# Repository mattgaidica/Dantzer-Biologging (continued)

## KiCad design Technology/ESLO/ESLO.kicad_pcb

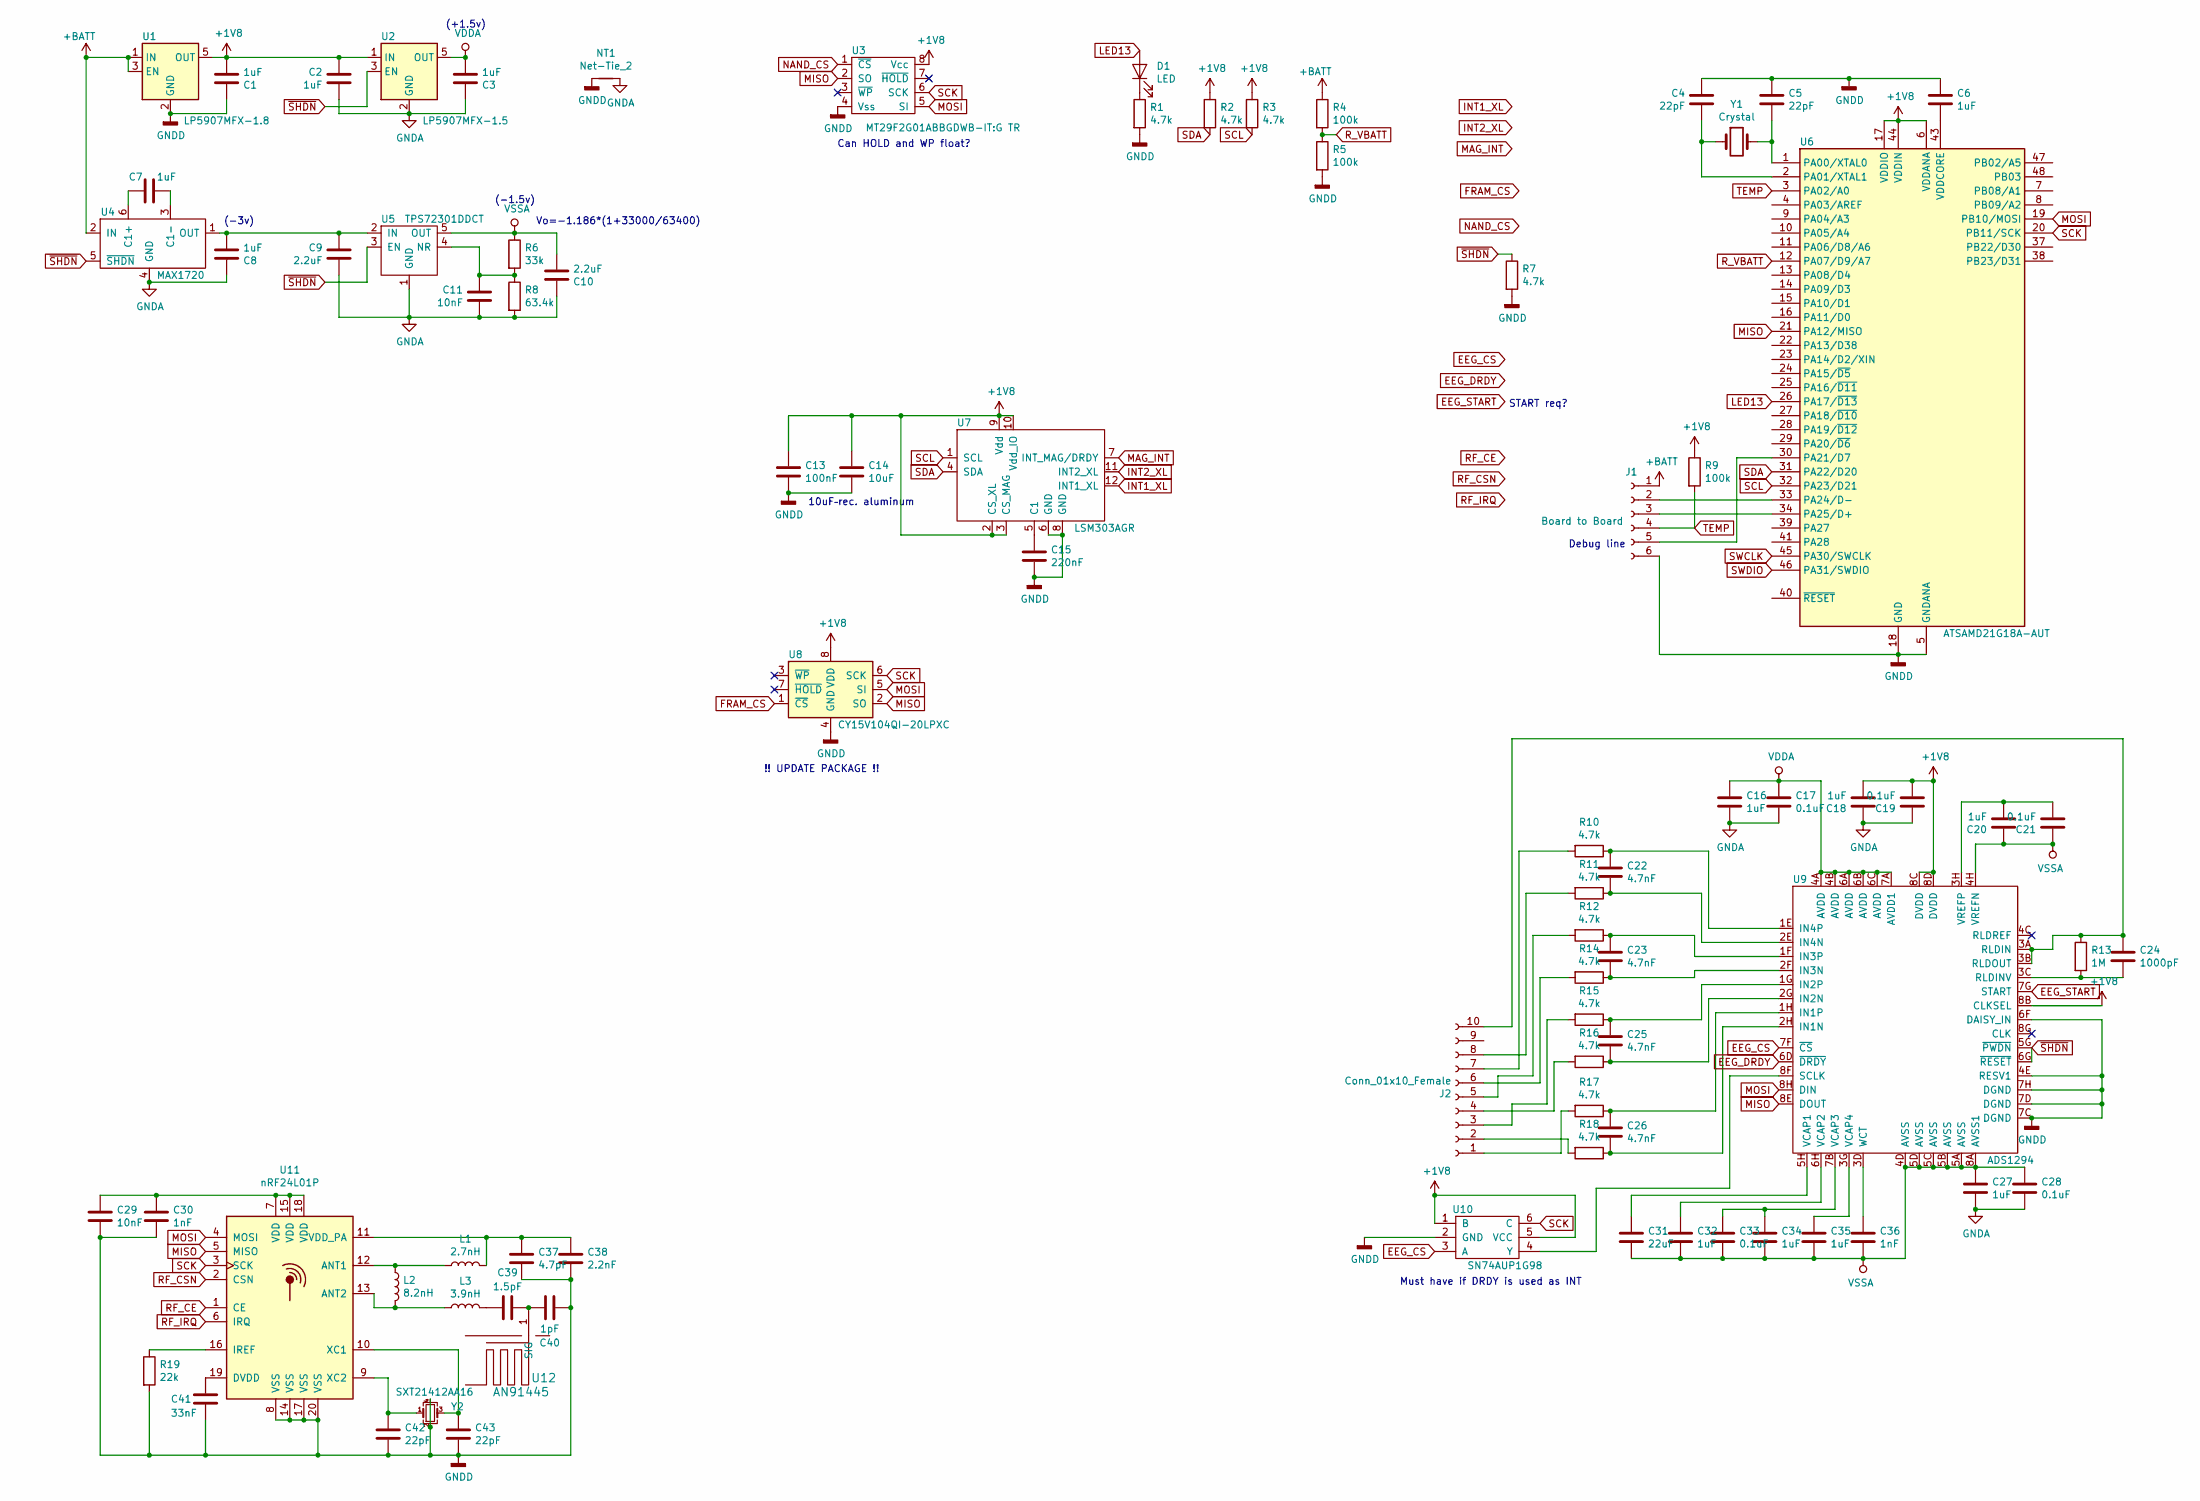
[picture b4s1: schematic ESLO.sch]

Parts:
C1, C2, C3, C6, C7, C8, C16, C18, C20, C27, C32, C34, C35: 1uF; C_0402_1005Metric
C4, C5, C42, C43: 22pF; C_0402_1005Metric
C9, C10: 2.2uF; C_0402_1005Metric
C11, C29: 10nF; C_0402_1005Metric
C13: 100nF; C_0402_1005Metric
C14: 10uF; C_0603_1608Metric; Digikey 490-14372-1-ND
C15: 220nF; C_0402_1005Metric
C17, C19, C21, C28, C33: 0.1uF; C_0402_1005Metric
C22, C23, C25, C26: 4.7nF; C_0402_1005Metric
C24: 1000pF; C_0402_1005Metric
C30, C36: 1nF; C_0402_1005Metric
C31: 22uF; C_0603_1608Metric; Digikey 1276-2867-1-ND
C37: 4.7pF; C_0402_1005Metric
C38: 2.2nF; C_0402_1005Metric
C39: 1.5pF; C_0402_1005Metric
C40: 1pF; C_0402_1005Metric
C41: 33nF; C_0402_1005Metric
D1: LED; LED_0603_1608Metric
J1: Board to Board; Hirose_DF52-6S-0.8H_1x06-1MP_P0.80mm_Horizontal
J2: Conn_01x10_Female; Hirose_DF52-10S-0.8H_1x10-1MP_P0.80mm_Horizontal
L1: 2.7nH; L_0402_1005Metric
L2: 8.2nH; L_0402_1005Metric
L3: 3.9nH; L_0402_1005Metric
NT1: Net-Tie_2; NetTie-2_SMD_Pad0.5mm
R1, R2, R3, R7, R16, R17, R18: 4.7k; R_0402_1005Metric
R4, R5, R9: 100k; LED_0402_1005Metric
R6: 33k; R_0402_1005Metric; Digikey A129645CT-ND
R8: 63.4k; R_0402_1005Metric; Digikey RHM63.4KBHCT-ND
R10, R11, R12, R14, R15: 4.7k; LED_0402_1005Metric
R13: 1M; LED_0402_1005Metric
R19: 22k; LED_0402_1005Metric
U1: LP5907MFX-1.8; SOT-23-5
U2: LP5907MFX-1.5; SOT-23-5; Digikey 296-40355-1-ND
U3: MT29F2G01ABBGDWB-IT:G TR; 8x6mm_WSON_UTSO; Digikey 557-1665-1-ND
U4: MAX1720; SOT-23-6
U5: TPS72301DDCT; SOT-23-5; Digikey 296-38438-1-ND
U6: ATSAMD21G18A-AUT; QFN-48-1EP_7x7mm_P0.5mm_EP5.15x5.15mm; Digikey ATSAMD21G18A-MFTCT-ND
U7: LSM303AGR; LGA-12_2x2mm_P0.5mm; Digikey 497-16527-1-ND
U8: CY15V104QI-20LPXC; DFN-8-1EP_3x3mm_P0.65mm_EP1.7x2.05mm
U9: ADS1294; BGA-64_8x8_8.0x8.0mm_ADS129x; Digikey 296-28024-1-ND
U10: SN74AUP1G98; SOT-563; Digikey 296-19087-1-ND
U11: nRF24L01P; QFN-20-1EP_4x4mm_P0.5mm_EP2.5x2.5mm
U12: AN91445; AN91445_MG
Y1: Crystal; Crystal_SMD_3215-2Pin_3.2x1.5mm; Digikey SER4103CT-ND
Y2: SXT21412AA16; SXT214

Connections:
+1V8: C1.1, C2.2, C13.1, C14.1, C18.2, C19.2, R2.1, R3.1, R9.1, U1.5 (OUT), U2.1 (IN), U3.8 (Vcc), U6.6 (VDDANA), U6.17 (VDDIO), U6.36 (VDDIO), U6.44 (VDDIN), U7.2 (CS_XL), U7.3 (CS_MAG), U7.9 (Vdd), U7.10 (Vdd_IO), U8.8 (VDD), U9.8B (CLKSEL), U9.8C (DVDD), U9.8D (DVDD), U10.1 (B), U10.5 (VCC)
D+: J1.3, U6.34 (PA25/D+)
D-: J1.2, U6.33 (PA24/D-)
EEG_CS: U6.15 (PA10/D1), U9.7F (~CS), U10.3 (A)
EEG_DRDY: U6.16 (PA11/D0), U9.6D (~DRDY)
EEG_START: U6.22 (PA13/D38), U9.7G (START)
FRAM_CS: U6.13 (PA08/D4), U8.1 (~CS)
GNDA: C2.1, C3.2, C8.2, C9.1, C10.2, C11.1, C16.2, C17.2, C18.1, C19.1, C27.2, C28.2, NT1.2, R8.2, U2.2 (GND), U4.4 (GND), U5.1 (GND)
GNDD: C1.2, C4.2, C5.1, C6.1, C13.2, C14.2, C15.1, C29.2, C30.2, C37.2, C38.2, C40.1, C41.1, C42.2, C43.2, J1.6, NT1.1, R1.2, R5.2, R7.2, R19.2, U1.2 (GND), U3.4 (Vss), U6.5 (GNDANA), U6.18 (GND), U6.35 (GND), U6.42 (GND), U7.6 (GND), U7.8 (GND), U8.4 (GND), U9.4E (RESV1), U9.6F (DAISY_IN), U9.7C (DGND), U9.7D (DGND), U9.7H (DGND), U10.2 (GND), U11.8 (VSS), U11.14 (VSS), U11.17 (VSS), U11.20 (VSS), U12.2, Y2.2, Y2.4
INT2_XL: U6.29 (PA20/~D6), U7.11 (INT2_XL)
LED13: D1.2 (A), U6.26 (PA17/~D13)
MAG_INT: U6.28 (PA19/~D12), U7.7 (INT_MAG/DRDY)
MISO: U3.2 (SO), U6.21 (PA12/MISO), U8.2 (SO), U9.8E (DOUT), U11.5 (MISO)
MOSI: U3.5 (SI), U6.19 (PB10/MOSI), U8.5 (SI), U9.8H (DIN), U11.4 (MOSI)
NAND_CS: U3.1 (~CS), U6.14 (PA09/D3)
unnamed: C4.1, U6.2 (PA01/XTAL1), Y1.1
unnamed: C5.2, U6.1 (PA00/XTAL0), Y1.2
unnamed: C6.2, U6.43 (VDDCORE)
unnamed: C7.1, U4.6 (C1+)
unnamed: C7.2, U4.3 (C1-)
unnamed: C8.1, C9.2, U4.1 (OUT), U5.2 (IN)
unnamed: C11.2, R6.2, R8.1, U5.4 (NR)
unnamed: C15.2, U7.5 (C1)
unnamed: C20.2, C21.2, U9.3H (VREFP)
unnamed: C22.1, R10.1, U9.1E (IN4P)
unnamed: C22.2, R11.1, U9.2E (IN4N)
unnamed: C23.1, R12.1, U9.1F (IN3P)
unnamed: C23.2, R14.1, U9.2F (IN3N)
unnamed: C24.1, J2.10, R13.1, U9.3A (RLDIN), U9.3B (RLDOUT)
unnamed: C24.2, R13.2, U9.3C (RLDINV)
unnamed: C25.1, R15.1, U9.1G (IN2P)
unnamed: C25.2, R16.1, U9.2G (IN2N)
unnamed: C26.1, R17.1, U9.1H (IN1P)
unnamed: C26.2, R18.1, U9.2H (IN1N)
unnamed: C31.1, U9.5H (VCAP1)
unnamed: C32.1, U9.6H (VCAP2)
unnamed: C33.1, C34.1, U9.7B (VCAP3)
unnamed: C35.1, U9.3G (VCAP4)
unnamed: C36.1, U9.3D (WCT)
unnamed: C37.1, C38.1, L1.2, U11.11 (VDD_PA)
unnamed: C39.1, L3.2
unnamed: C39.2, C40.2, U12.1
unnamed: C41.2, U11.19 (DVDD)
unnamed: C42.1, U11.9 (XC2), Y2.1
unnamed: C43.1, U11.10 (XC1), Y2.3
unnamed: D1.1 (K), R1.1
unnamed: J2.1, R17.2
unnamed: J2.2, R18.2
unnamed: J2.3, R15.2
unnamed: J2.4, R16.2
unnamed: J2.5, R12.2
unnamed: J2.6, R14.2
unnamed: J2.7, R10.2
unnamed: J2.8, R11.2
unnamed: L1.1, L2.1, U11.12 (ANT1)
unnamed: L2.2, L3.1, U11.13 (ANT2)
unnamed: R19.1, U11.16 (IREF)
unnamed: U9.8F (SCLK), U10.4 (Y)
RF_CE: U6.24 (PA15/~D5), U11.1 (CE)
RF_CSN: U6.23 (PA14/D2/XIN), U11.2 (CSN)
RF_IRQ: U6.25 (PA16/~D11), U11.6 (IRQ)
R_VBATT: R4.2, R5.1, U6.12 (PA07/D9/A7)
SCK: U3.6 (SCK), U6.20 (PB11/SCK), U8.6 (SCK), U10.6 (C), U11.3 (SCK)
SCL: R3.2, U6.32 (PA23/D21), U7.1 (SCL)
SDA: R2.2, U6.31 (PA22/D20), U7.4 (SDA)
SWCLK: U6.45 (PA30/SWCLK); also elsewhere on the board
SWDIO: U6.46 (PA31/SWDIO); also elsewhere on the board
TEMP: J1.4, R9.2, U6.3 (PA02/A0), U6.10 (PA05/A4)
VDDA: C3.1, C16.1, C17.1, U2.5 (OUT), U9.4A (AVDD), U9.4B (AVDD), U9.6A (AVDD), U9.6B (AVDD), U9.6C (AVDD), U9.7A (AVDD1)
VSSA: C10.1, C20.1, C21.1, C27.1, C28.1, C31.2, C32.2, C33.2, C34.2, C35.2, C36.2, R6.1, U5.5 (OUT), U9.4D (AVSS), U9.4H (VREFN), U9.5A (AVSS), U9.5B (AVSS), U9.5C (AVSS), U9.5D (AVSS), U9.8A (AVSS1)
~SHDN: R7.1, U2.3 (EN), U4.5 (~SHDN), U5.3 (EN), U6.11 (PA06/D8/A6), U9.5G (~PWDN), U9.6G (~RESET)

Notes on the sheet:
Vo=-1.186*(1+33000/63400)
Can HOLD and WP float?
(-1.5v)
(+1.5v)
10uF–rec. aluminum
Must have if DRDY is used as INT
!! UPDATE PACKAGE !!
(-3v)
Debug line
START req?

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
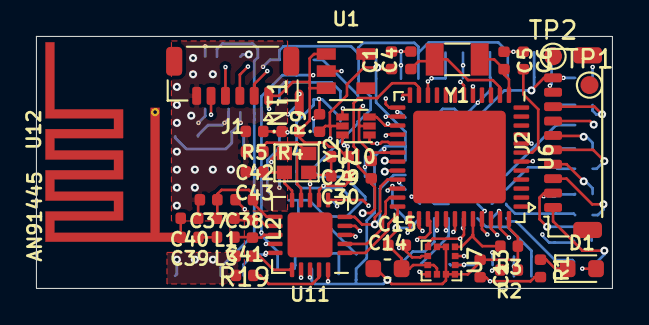
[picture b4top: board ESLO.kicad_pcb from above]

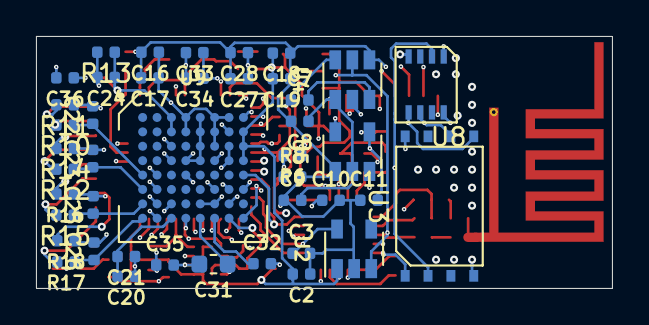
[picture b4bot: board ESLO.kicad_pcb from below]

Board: 4 copper layers, 32.0 x 14.0 mm, 84 parts (43 on the bottom side), 74 nets.

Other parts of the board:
TP1, TP2: TestPoint; TestPoint_Pad_D1.0mm

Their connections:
SWCLK: TP1.1; also elsewhere on the board
SWDIO: TP2.1; also elsewhere on the board

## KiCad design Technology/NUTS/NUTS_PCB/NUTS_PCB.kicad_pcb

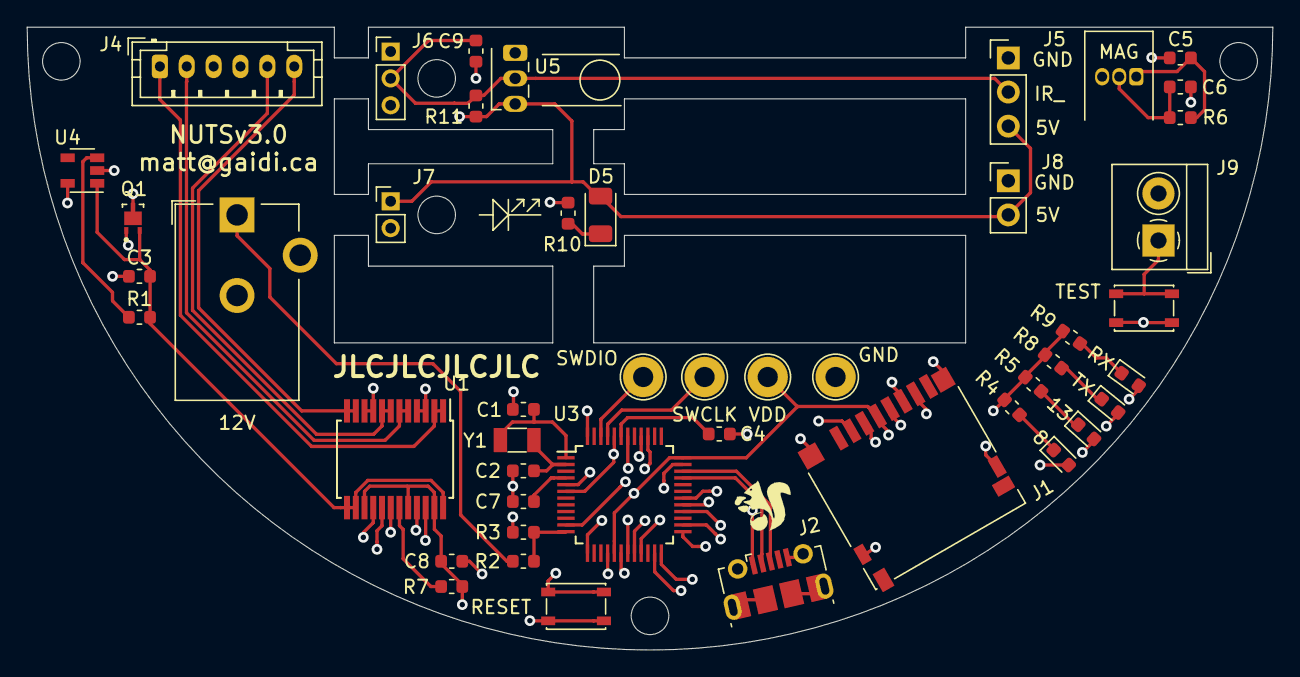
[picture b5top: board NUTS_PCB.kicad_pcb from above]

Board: 4 copper layers, 92.7 x 46.4 mm, 47 parts (1 on the bottom side), 41 nets.

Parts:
C1, C2: 22pF; C_0603_1608Metric
C3, C8: 10uF; C_0603_1608Metric
C4, C7: 1uF; C_0603_1608Metric
C5, C6: 100nF; C_0603_1608Metric
C9: .22uF; C_0603_1608Metric
D1, D2, D3, D4: LED; LED_0603_1608Metric
D5: IR_LED; LED_1206_3216Metric
J1: Micro_SD_Card_Det_Hirose_DM3AT; microSD_HC_Hirose_DM3D-SF
J2: USB_B_Micro; USB_Micro-B_Molex-105017-0001
J3: Jack-DC; BarrelJack_CUI_PJ-102AH_Horizontal
J4: Conn_01x06_Female; JST_PH_B6B-PH-K_1x06_P2.00mm_Vertical
J5: Conn_01x03_Male; PinHeader_1x03_P2.54mm_Vertical
J6: Conn_01x03_Female; PinHeader_1x03_P2.00mm_Vertical
J7: Conn_01x02_Female; PinHeader_1x02_P2.00mm_Vertical
J8: Conn_01x02_Male; PinHeader_1x02_P2.54mm_Vertical
J9: Screw_Terminal_01x02; TerminalBlock_4Ucon_1x02_P3.50mm_Horizontal
Q1: DMG3415UFY4Q; TRANS_DMG3415UFY4Q-7
R1, R2, R6, R7: 10K; R_0603_1608Metric
R3, R4, R5, R8, R9: 1K; R_0603_1608Metric
R10: 220; R_0603_1608Metric
R11: 390; R_0603_1608Metric
SW1, SW2: SW_SPST; SW_SPST_PTS810
TP1: SWDIO; TestPoint_Loop_D2.54mm_Drill1.5mm_Beaded
TP2: SWCLK; TestPoint_Loop_D2.54mm_Drill1.5mm_Beaded
TP3: VDD; TestPoint_Loop_D2.54mm_Drill1.5mm_Beaded
TP4: GND; TestPoint_Loop_D2.54mm_Drill1.5mm_Beaded
U1: TB6612FNG; SSOP-24_5.3x8.2mm_P0.65mm
U2: US5881; TO-92Flat
U3: ATSAMD21G18A-AUT; TQFP-48_7x7mm_P0.5mm
U4: SPX3819M5-L; SOT-23-5
U5: QSE159; ONSemi_QSE15x
Y1: Crystal; Crystal_SMD_3215-2Pin_3.2x1.5mm

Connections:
+5V: C8.1, D5.2, J2.1, J5.3, J6.1, J7.1, J8.2, R7.2, R11.1, U1.15, U1.20, U1.23, U5.3
+12V: C3.1, Q1.2, R1.1, U1.13, U1.14, U1.24, U4.1
+BATT: J3.1, Q1.3, R2.1
AIN1: U1.21, U3.29
AIN2: U1.22, U3.30
BIN1: U1.17, U3.25
BIN2: U1.16, U3.28
D0: J9.1, SW2.2, U3.16
D2: C6.1, R6.2, U2.2, U3.23
D8: D1.2, U3.11
D9: R2.2, R3.1, U3.12
D13: D2.2, U3.26
D+: J2.3, U3.34
D-: J2.2, U3.33
GND: C1.2, C2.2, C3.2, C4.2, C5.2, C6.2, C7.2, C8.2, C9.2, J1.6, J1.11, J2.5, J2.6, J3.2, J4.3, J4.4, J5.1, J6.3, J7.2, J8.1, J9.2, Q1.1, R3.2, R4.2, R5.2, R8.2, R9.2, R10.2, SW1.1, SW2.1, TP4.1, U1.3, U1.4, U1.9, U1.10, U1.18, U2.3, U3.5, U3.18, U3.35, U3.42, U4.2, U5.1
IR_DET: C9.1, J5.2, J6.2, R11.2, U3.24, U5.2
MISO: J1.7, U3.21
MOSI: J1.3, U3.19
unnamed: C1.1, U3.1, Y1.1
unnamed: C2.1, U3.2, Y1.2
unnamed: C4.1, U3.43
unnamed: C7.1, U3.4
unnamed: D1.1, R4.1
unnamed: D2.1, R5.1
unnamed: D3.1, R8.1
unnamed: D4.1, R9.1
unnamed: D5.1, R10.1
unnamed: J4.1, U1.1, U1.2
unnamed: J4.2, U1.5, U1.6
unnamed: J4.5, U1.7, U1.8
unnamed: J4.6, U1.11, U1.12
unnamed: R1.2, U4.3
unnamed: R7.1, U1.19
unnamed: SW1.2, U3.40
unnamed: TP1.1, U3.46
unnamed: TP2.1, U3.45
RXLED: D4.2, U3.48
SCK: J1.5, U3.20
SD_CS: J1.2, U3.13
TXLED: D3.2, U3.39
VDD: C5.1, J1.4, R6.1, TP3.1, U2.1, U3.6, U3.17, U3.36, U3.44, U4.5

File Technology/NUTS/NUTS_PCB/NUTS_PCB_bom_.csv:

Component,Description,Part,References,Value,Footprint,Quantity Per PCB,Datasheet,digikey
1,Unpolarized capacitor,C,C9,.22uF,C_0603_1608Metric,1,~,399-1102-1-ND
2,Unpolarized capacitor,C,C5 C6,100nF,C_0603_1608Metric,2,~,399-1100-1-ND
3,Unpolarized capacitor,C,C3 C8,10uF,C_0603_1608Metric,2,~,490-10474-1-ND
4,Unpolarized capacitor,C,C4 C7,1uF,C_0603_1608Metric,2,~,399-1100-1-ND
5,Unpolarized capacitor,C,C1 C2,22pF,C_0603_1608Metric,2,~,399-7874-1-ND
6,Light emitting diode,LED,D5,IR_LED,LED_1206_3216Metric,1,~,1497-1422-1-ND
7,Light emitting diode,LED,D1 D2 D3 D4,LED,LED_0603_1608Metric,4,~,
8,"Generic connector, single row, 01x02, script generated (kicad-library-utils/schlib/autogen/connector/)",Conn_01x02_Female,J7,Conn_01x02_Female,PinHeader_1x02_P2.00mm_Vertical,1,~,
9,"Generic connector, single row, 01x02, script generated (kicad-library-utils/schlib/autogen/connector/)",Conn_01x02_Male,J8,Conn_01x02_Male,PinHeader_1x02_P2.54mm_Vertical,1,~,A19430-ND
10,"Generic connector, single row, 01x03, script generated (kicad-library-utils/schlib/autogen/connector/)",Conn_01x03_Female,J6,Conn_01x03_Female,PinHeader_1x03_P2.00mm_Vertical,1,~,
11,"Generic connector, single row, 01x03, script generated (kicad-library-utils/schlib/autogen/connector/)",Conn_01x03_Male,J5,Conn_01x03_Male,PinHeader_1x03_P2.54mm_Vertical,1,~,A19423-ND
12,"Generic connector, single row, 01x06, script generated (kicad-library-utils/schlib/autogen/connector/)",Conn_01x06_Female,J4,Conn_01x06_Female,JST_PH_B6B-PH-K_1x06_P2.00mm_Vertical,1,~,455-2923-ND
13,DC Barrel Jack,Jack-DC,J3,Jack-DC,BarrelJack_CUI_PJ-102AH_Horizontal,1,~,CP-102A-ND
14,Micro SD Card Socket with card detection pins,Micro_SD_Card_Det_Hirose_DM3AT,J1,Micro_SD_Card_Det_Hirose_DM3AT,microSD_HC_Hirose_DM3D-SF,1,https://www.hirose.com/product/en/download_file/key_name/DM3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,HR1964CT-ND
15,"Generic screw terminal, single row, 01x02, script generated (kicad-library-utils/schlib/autogen/connector/)",Screw_Terminal_01x02,J9,Screw_Terminal_01x02,TerminalBlock_4Ucon_1x02_P3.50mm_Horizontal,1,~,277-1721-ND
16,USB Micro Type B connector,USB_B_Micro,J2,USB_B_Micro,USB_Micro-B_Molex-105017-0001,1,~,WM1399CT-ND
17,"P-JFET transistor, gate/source/drain",Q_PJFET_GSD,Q1,DMG3415UFY4Q,TRANS_DMG3415UFY4Q-7,1,~,DMG3415UFY4Q-7DICT-ND
18,Resistor,R,R1 R2 R6 R7,10K,R_0603_1608Metric,4,~,311-10KGRCT-ND
19,Resistor,R,R3 R4 R5 R8 R9,1K,R_0603_1608Metric,5,~,311-1.0KGRCT-ND
20,Resistor,R,R10,220,R_0603_1608Metric,1,~,311-220HRCT-ND
21,Resistor,R,R11,390,R_0603_1608Metric,1,~,A129683CT-ND
22,Single Pole Single Throw (SPST) switch,SW_SPST,SW1 SW2,SW_SPST,SW_SPST_PTS810,2,~,CKN10502CT-ND
23,"SAM D21 Microchip SMART ARM-based Flash MCU, 48Mhz, 256K Flash, 32K SRAM, TQFP-48",ATSAMD21G18A-AUT,U3,ATSAMD21G18A-AUT,TQFP-48_7x7mm_P0.5mm,1,http://ww1.microchip.com/downloads/en/DeviceDoc/SAMD21-Famil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,ATSAMD21G18A-AUTCT-ND
24,Plastic Silicon Photosensor,QSE159,U5,QSE159,ONSemi_QSE15x,1,http://www.onsemi.com/pub/Collateral/QSE159-D.pdf,QSE159-ND
25,"500mA Low drop-out regulator, Adjustable, SOT-23-5",SPX3819M5-L,U4,SPX3819M5-L,SOT-23-5,1,https://www.exar.com/content/document.ashx?id=22106&language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,1016-1873-1-ND
26,,TB6612FNG,U1,TB6612FNG,SSOP-24_5.3x8.2mm_P0.65mm,1,,TB6612FNGC8ELCT-ND
27,"Hall effect switch, unipolar, Bop=100G, Brp=45G, -40C to +85C",A1101ELHL,U2,US5881,TO-92Flat,1,http://www.allegromicro.com/en/Products/Part_Numbers/1101/1101.pdf,US5881LUA-AAA-000-BU-ND
28,Two pin crystal,Crystal,Y1,Crystal,Crystal_SMD_3215-2Pin_3.2x1.5mm,1,~,SER4103CT-ND





Component Groups:,28
Component Count:,43
Fitted Components:,43
Number of PCBs:,1
Total components:,43
Schematic Version:,
Schematic Date:,
BoM Date:,"Tuesday, March 24, 2020 at 10:09:05 PM"
Schematic Source:,/Users/matt/Box Sync/Biologging/Technology/NUTS/NUTS_PCB/NUTS_PCB.sch
KiCad Version:,Eeschema (5.1.5-0-10_14)

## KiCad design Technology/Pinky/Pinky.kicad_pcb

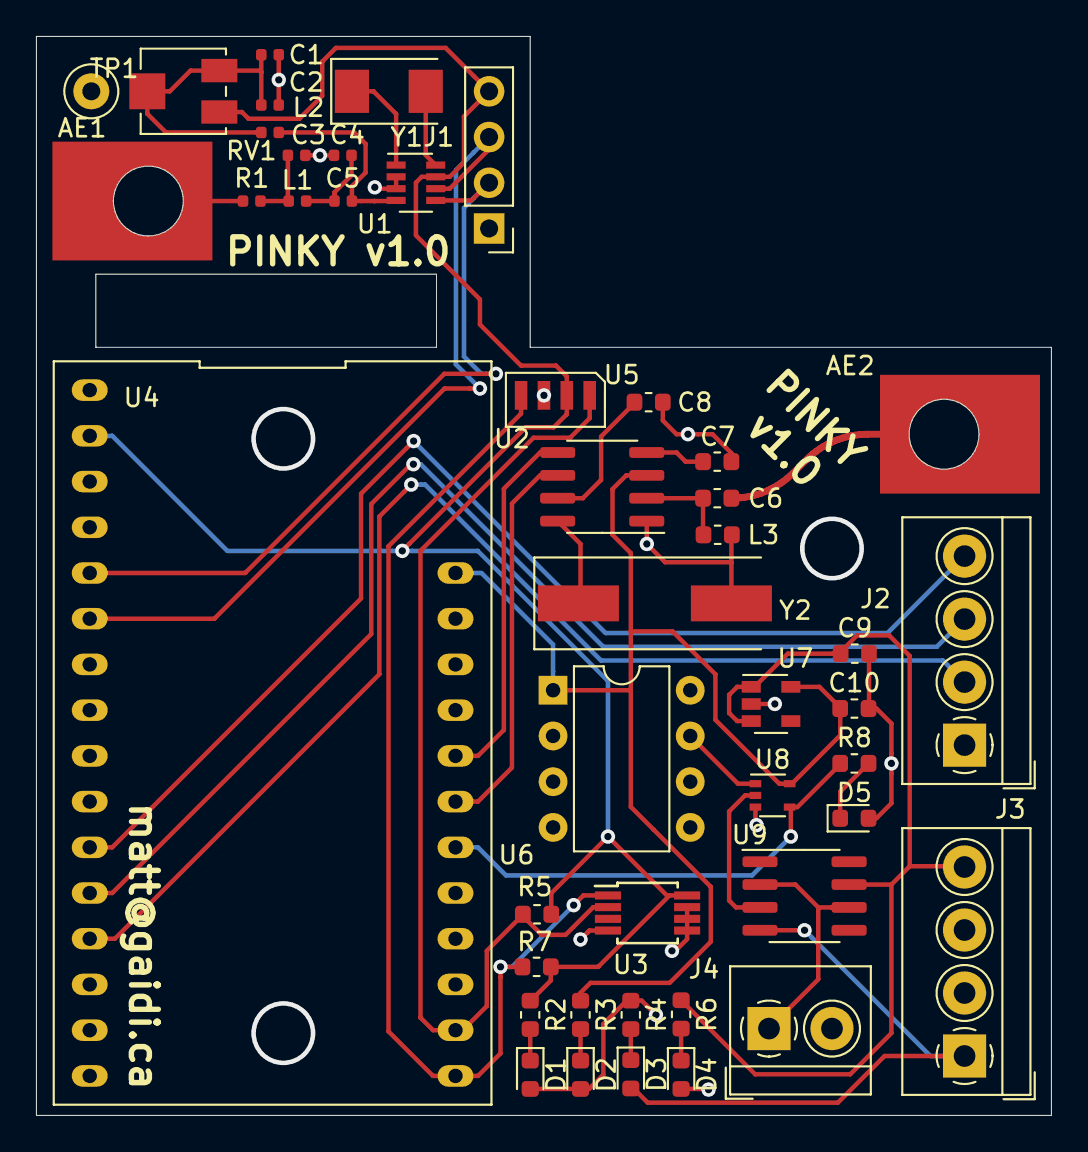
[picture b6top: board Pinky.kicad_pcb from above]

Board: 2 copper layers, 56.4 x 59.9 mm, 45 parts (0 on the bottom side), 35 nets.

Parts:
AE1, AE2: Antenna; Linx_Ant_Screw
C1: 680pF; C_0402_1005Metric
C2: 220pF; C_0402_1005Metric
C3, C5: 15pF; C_0402_1005Metric
C4: 22pF; C_0402_1005Metric
C6: 1.8pF; C_0603_1608Metric
C7: .039uF; C_0603_1608Metric
C8, C10: 2.2uF; C_0603_1608Metric
C9: 1uF; C_0603_1608Metric
D1: +3.3V; D_0603_1608Metric
D2: +5V; D_0603_1608Metric
D3: -6V; D_0603_1608Metric
D4: +6V; D_0603_1608Metric
D5: PINK_EN; D_0603_1608Metric
J1: TX CONN; PinHeader_1x04_P2.54mm_Vertical
J2: SPI CONN; TerminalBlock_4Ucon_1x04_P3.50mm_Horizontal
J3: 6V BATT; TerminalBlock_4Ucon_1x04_P3.50mm_Horizontal
J4: SPEAKER; TerminalBlock_4Ucon_1x02_P3.50mm_Horizontal
L1: 22nH; L_0402_1005Metric
L2: 27nH; L_0402_1005Metric
L3: 56nH; L_0603_1608Metric
R1: 0; R_0402_1005Metric
R2, R3, R4, R6, R8: 2.2k; R_0603_1608Metric
R5, R7: 4.7k; R_0603_1608Metric
RV1: 5k; Potentiometer_Bourns_3314J_Vertical
TP1: TP_GND; TestPoint_Loop_D2.50mm_Drill1.0mm
U1: MAX1472; SOT-23-8
U2: MICRF007; SOIC-8_3.9x4.9mm_P1.27mm
U3: MCP9808_MSOP; MSOP-8_3x3mm_P0.65mm
U4: Adalogger; Adafruit_feather
U5: VEML7700
U6: NOISE2; DIP-8_W7.62mm
U7: AP2204K-5.0; SOT-23-5
U8: SN74LVC; SOT-353_SC-70-5
U9: TL071; SOIC-8_3.9x4.9mm_P1.27mm
Y1: 9.84375MHz; Crystal_SMD_Abracon_ABM3-2Pin_5.0x3.2mm
Y2: 4.8970MHz; Crystal_SMD_HC49-SD

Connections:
+3V3: J1.4, R2.1, R5.1, R7.1, RV1.1, U1.7, U3.8, U4.2, U5.2
+5V: C10.1, R3.1, U2.3, U4.28, U6.1, U7.5, U8.5
+6V: C9.1, J3.4, R6.1, U7.1, U7.3, U9.7
-6V: D3.2, J3.1, U9.4
GND: C1.1, C2.1, C3.1, C4.1, C7.1, C8.1, C9.2, C10.2, D1.2, D2.2, D4.2, D5.2, J1.1, J2.1, J3.2, J3.3, J4.2, L3.1, R4.1, TP1.1, U1.2, U1.3, U2.1, U3.4, U3.5, U3.6, U3.7, U4.4, U4.16, U5.3, U6.8, U7.2, U8.3, Y2.2
unnamed: AE1.1, R1.2
unnamed: AE2.1, C6.1
unnamed: C1.2, C2.2, L2.2, RV1.2, RV1.3
unnamed: C3.2, L1.1, R1.1
unnamed: C4.2, C5.2, L1.2
unnamed: C5.1, L2.1, U1.4
unnamed: C6.2, L3.2, U2.2
unnamed: C7.2, U2.4
unnamed: C8.2, U2.7
unnamed: D1.1, R2.2
unnamed: D2.1, R3.2
unnamed: D3.1, R4.2
unnamed: D4.1, R6.2
unnamed: D5.1, R8.2
unnamed: J1.2, U1.5, U4.5
unnamed: J1.3, U1.6, U4.6
unnamed: J2.2, U4.13
unnamed: J2.3, U4.12
unnamed: J2.4, U4.11
unnamed: J4.1, U9.2, U9.6
unnamed: R8.1, U4.22, U8.4
unnamed: U1.1, Y1.1
unnamed: U1.8, Y1.2
unnamed: U2.5, U4.24
unnamed: U2.6, U4.23
unnamed: U2.8, Y2.1
unnamed: U6.7, U8.1
unnamed: U8.2, U9.3
SCL: R5.2, U3.2, U4.18, U5.1
SDA: R7.2, U3.1, U4.17, U5.4

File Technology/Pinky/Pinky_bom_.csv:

Component,Description,Part,References,Value,Footprint,Quantity Per PCB,Datasheet,Digikey
1,Antenna,Antenna,AE1 AE2,Antenna,Linx_Ant_Screw,2,~,ANT-315-PW-LP-ND
2,Unpolarized capacitor,C,C7,.039uF,C_0603_1608Metric,1,~,311-4072-1-ND
3,Unpolarized capacitor,C,C6,1.8pF,C_0603_1608Metric,1,~,490-9667-2-ND
4,Unpolarized capacitor,C,C3 C5,15pF,C_0402_1005Metric,2,~,399-8947-1-ND
5,Unpolarized capacitor,C,C9,1uF,C_0603_1608Metric,1,~,1276-1182-1-ND
6,Unpolarized capacitor,C,C8 C10,2.2uF,C_0603_1608Metric,2,~,399-7886-1-ND
7,Unpolarized capacitor,C,C2,220pF,C_0402_1005Metric,1,~,490-6220-1-ND
8,Unpolarized capacitor,C,C4,22pF,C_0402_1005Metric,1,~,490-5868-1-ND
9,Unpolarized capacitor,C,C1,680pF,C_0402_1005Metric,1,~,399-1027-1-ND
10,Light emitting diode,LED,D1,+3.3V,D_0603_1608Metric,1,~,732-4971-1-ND
11,Light emitting diode,LED,D2,+5V,D_0603_1608Metric,1,~,732-4971-1-ND
12,Light emitting diode,LED,D4,+6V,D_0603_1608Metric,1,~,732-4971-1-ND
13,Light emitting diode,LED,D3,-6V,D_0603_1608Metric,1,~,732-4971-1-ND
14,Light emitting diode,LED,D5,PINK_EN,D_0603_1608Metric,1,~,732-4978-1-ND
15,"Generic connector, single row, 01x02, script generated (kicad-library-utils/schlib/autogen/connector/)",Conn_01x02_Female,J4,SPEAKER,TerminalBlock_4Ucon_1x02_P3.50mm_Horizontal,1,~,277-1860-ND
16,"Generic screw terminal, single row, 01x04, script generated (kicad-library-utils/schlib/autogen/connector/)",Screw_Terminal_01x04,J2 J3,SPI CONN,TerminalBlock_4Ucon_1x04_P3.50mm_Horizontal,2,~,277-1860-ND
17,"Generic connector, single row, 01x04, script generated (kicad-library-utils/schlib/autogen/connector/)",Conn_01x04_Male,J1,TX CONN,PinHeader_1x04_P2.54mm_Vertical,1,~,
18,Inductor,L,L1,22nH,L_0402_1005Metric,1,~,712-1455-1-ND
19,Inductor,L,L2,27nH,L_0402_1005Metric,1,~,712-1413-1-ND
20,Capacitor symbol for simulation only,INDUCTOR,L3,56nH,L_0603_1608Metric,1,~,712-1443-1-ND
21,Resistor,R,R1,0,R_0402_1005Metric,1,~,1276-3480-1-ND
22,Resistor,R,R2 R3 R4 R6 R8,2.2k,R_0603_1608Metric,5,~,P2.2KGCT-ND
23,Resistor,R,R5 R7,4.7k,R_0603_1608Metric,2,~,RR08P4.7KDCT-ND
24,Potentiometer,R_POT,RV1,5k,Potentiometer_Bourns_3314J_Vertical,1,~,ST4ETA502CT-ND
25,"150mA low dropout linear regulator, wide input voltage range, 5.0V fixed positive output, SOT-23-5 package",AP2204K-5.0,U7,AP2204K-5.0,SOT-23-5,1,https://www.diodes.com/assets/Datasheets/AP2204.pdf,AP2204K-5.0TRG1DICT-ND
26,,Adalogger,U4,Adalogger,Adafruit_feather,1,,1528-1539-ND
27,,MAX1472,U1,MAX1472,SOT-23-8,1,,MAX1472AKA+TCT-ND
28,Microchip Technology Digital Temperature Sensor MSOP,MCP9804_MSOP,U3,MCP9808_MSOP,MSOP-8_3x3mm_P0.65mm,1,http://ww1.microchip.com/downloads/en/DeviceDoc/22203b.pdf,MCP9808T-E/MSCT-ND
29,,MICRF007,U2,MICRF007,SOIC-8_3.9x4.9mm_P1.27mm,1,,576-1334-ND
30,,NOISE2,U6,NOISE2,DIP-8_W7.62mm,1,,AE9986-ND
31,,SN74LVC,U8,SN74LVC,SOT-353_SC-70-5,1,,296-13254-1-ND
32,"Single Low-Noise JFET-Input Operational Amplifiers, DIP-8/SOIC-8",TL071,U9,TL071,SOIC-8_3.9x4.9mm_P1.27mm,1,http://www.ti.com/lit/ds/symlink/tl071.pdf,296-14994-1-ND
33,,VEML7700,U5,VEML7700,VEML7700,1,,VEML7700CT-ND
34,Two pin crystal,Crystal,Y2,4.8970MHz,Crystal_SMD_HC49-SD,1,~,535-9688-1-ND
35,Two pin crystal,Crystal,Y1,9.84375MHz,Crystal_SMD_Abracon_ABM3-2Pin_5.0x3.2mm,1,~,535-13417-1-ND





Component Groups:,35
Component Count:,44
Fitted Components:,44
Number of PCBs:,1
Total components:,44
Schematic Version:,
Schematic Date:,
BoM Date:,"Tuesday, June 30, 2020 at 06:02:59 PM"
Schematic Source:,/Users/matt/Box Sync/Biologging/Technology/Pinky/Pinky.sch
KiCad Version:,Eeschema (5.1.5-0-10_14)
